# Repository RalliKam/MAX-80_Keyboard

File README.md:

# LOBO MAX-80 · Keyboard Logic Board

This KiCad 10 project recreates the keyboard logic board from sheet 5 of the original LOBO MAX-80 schematics. The board scans the keyboard matrix and connects the mainboard to the hard disk and parallel printer interfaces. It also carries the boot-selection DIP switch and reset button.

## Opening the project

Open [MAX-80-Keyboard.kicad_pro](MAX-80-Keyboard.kicad_pro) in KiCad 10. The [schematic](MAX-80-Keyboard.kicad_sch) shows the switch matrix and interface logic. The [PCB layout](MAX-80-Keyboard.kicad_pcb) contains 106 footprints, including 76 keyboard switches. PCB routing is still pending.

## Keyboard layout

The rebuild uses plate-mounted Cherry MX switches on a 19.05 mm pitch. The staggered rows follow the reference photo, with F1–F4 down the left side of the numeric keypad and Enter in its lower-right corner.

| Keys | Count | Keycap width |
| --- | ---: | ---: |
| Letters, digits, punctuation, and other single-width keys | 72 | 1u |
| Return and both Shift keys | 3 | 1.5u |
| Space bar | 1 | 8u |

The wide key sizes are estimates from the photo. The space bar stabilizer spacing and fit to the original case still need a physical check.

The numeric keypad shares matrix positions with the main keyboard. Switches K66–K76 implement the keypad digits and decimal point, each wired in parallel with its counterpart. Keypad Enter shares the Return matrix position. The original matrix is documented on page TS-17 of the [MAX-80 Technical Reference Manual](../MAX-80_MAINBOARD/Tech_Ref_Manual_Updated.pdf#page=65).

## Board connections

| Connector | Function | Footprint |
| --- | --- | --- |
| J7 | Mainboard interface | 34-pin male header, 2 × 17, 2.54 mm pitch |
| J8 | Winchester hard disk interface | 50-contact card edge |
| J9 | Parallel printer interface | 34-contact card edge |

## Libraries and original drawings

The project includes two [symbol libraries](sym-lib-table). The [keyboard footprint library](MAX80_KeyboardParts.pretty) contains the two card-edge connectors, reset switch, DO-7 diode, and 8u space bar footprint. Other parts use the standard KiCad libraries.

- [Original schematic, sheet 5](../MAX-80_MAINBOARD/5.png)
- [Original keyboard logic board placement drawing](../MAX-80_MAINBOARD/Keyboard%20logic%20board.png)
- [Companion CPU Logic Board project](../MAX-80_MAINBOARD/README.md)

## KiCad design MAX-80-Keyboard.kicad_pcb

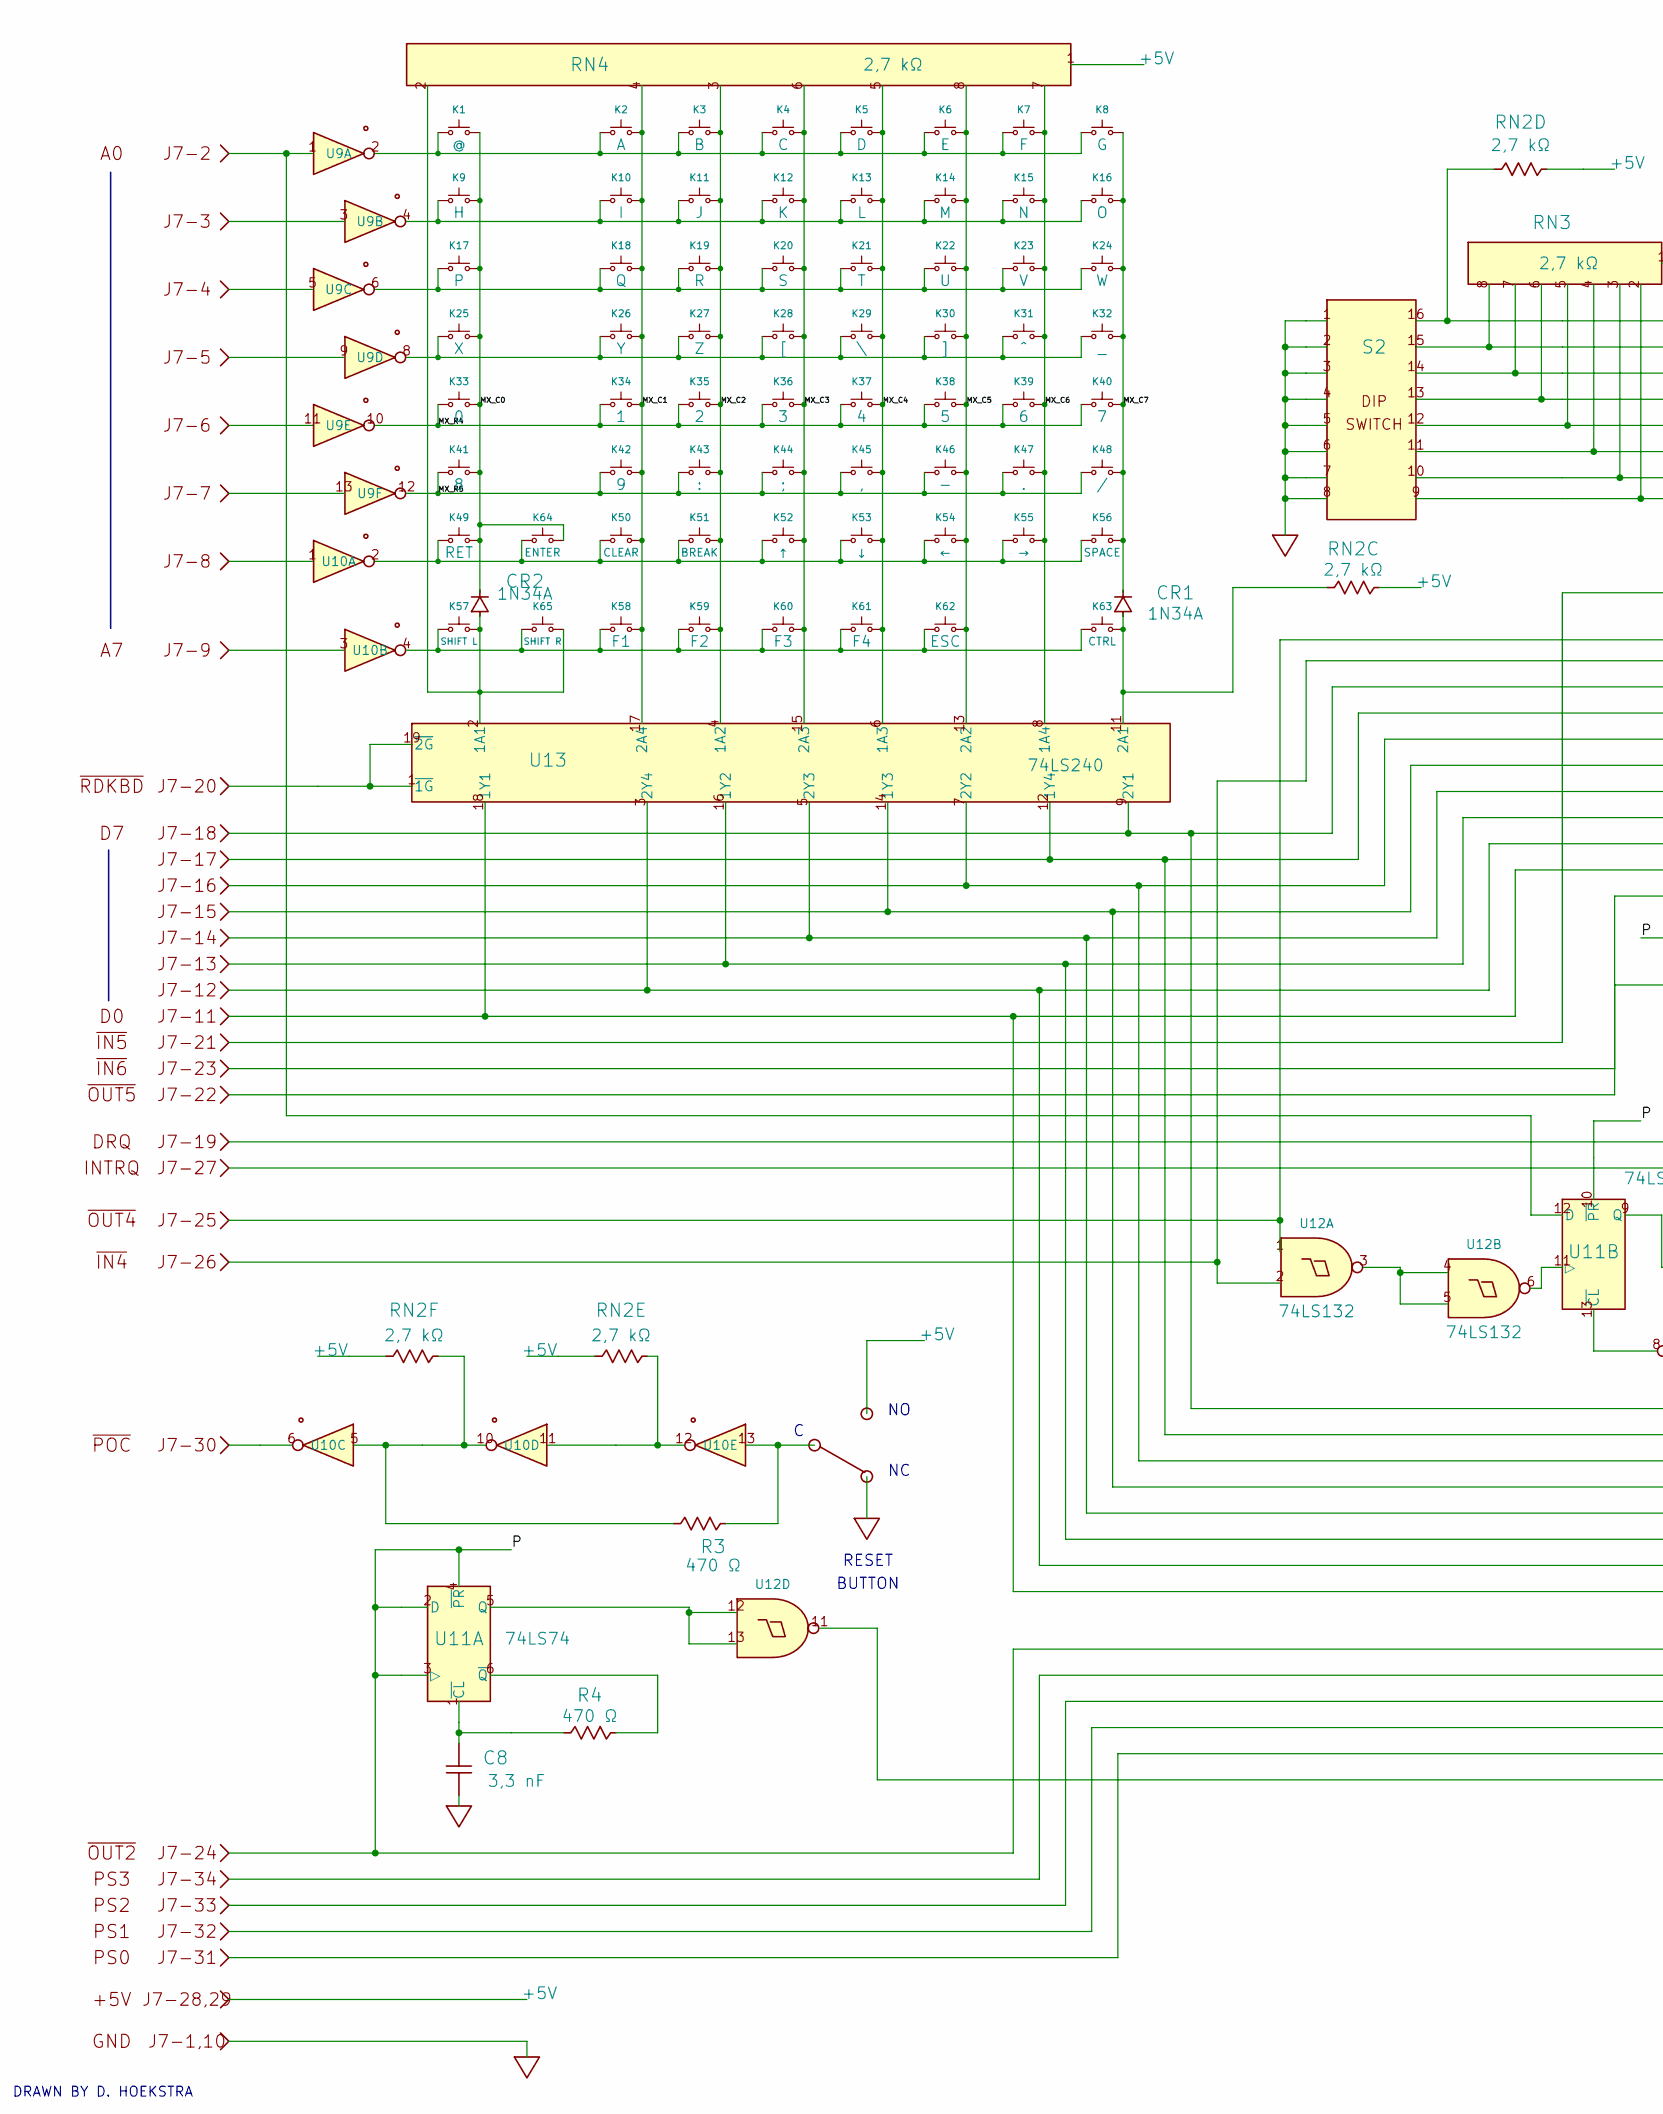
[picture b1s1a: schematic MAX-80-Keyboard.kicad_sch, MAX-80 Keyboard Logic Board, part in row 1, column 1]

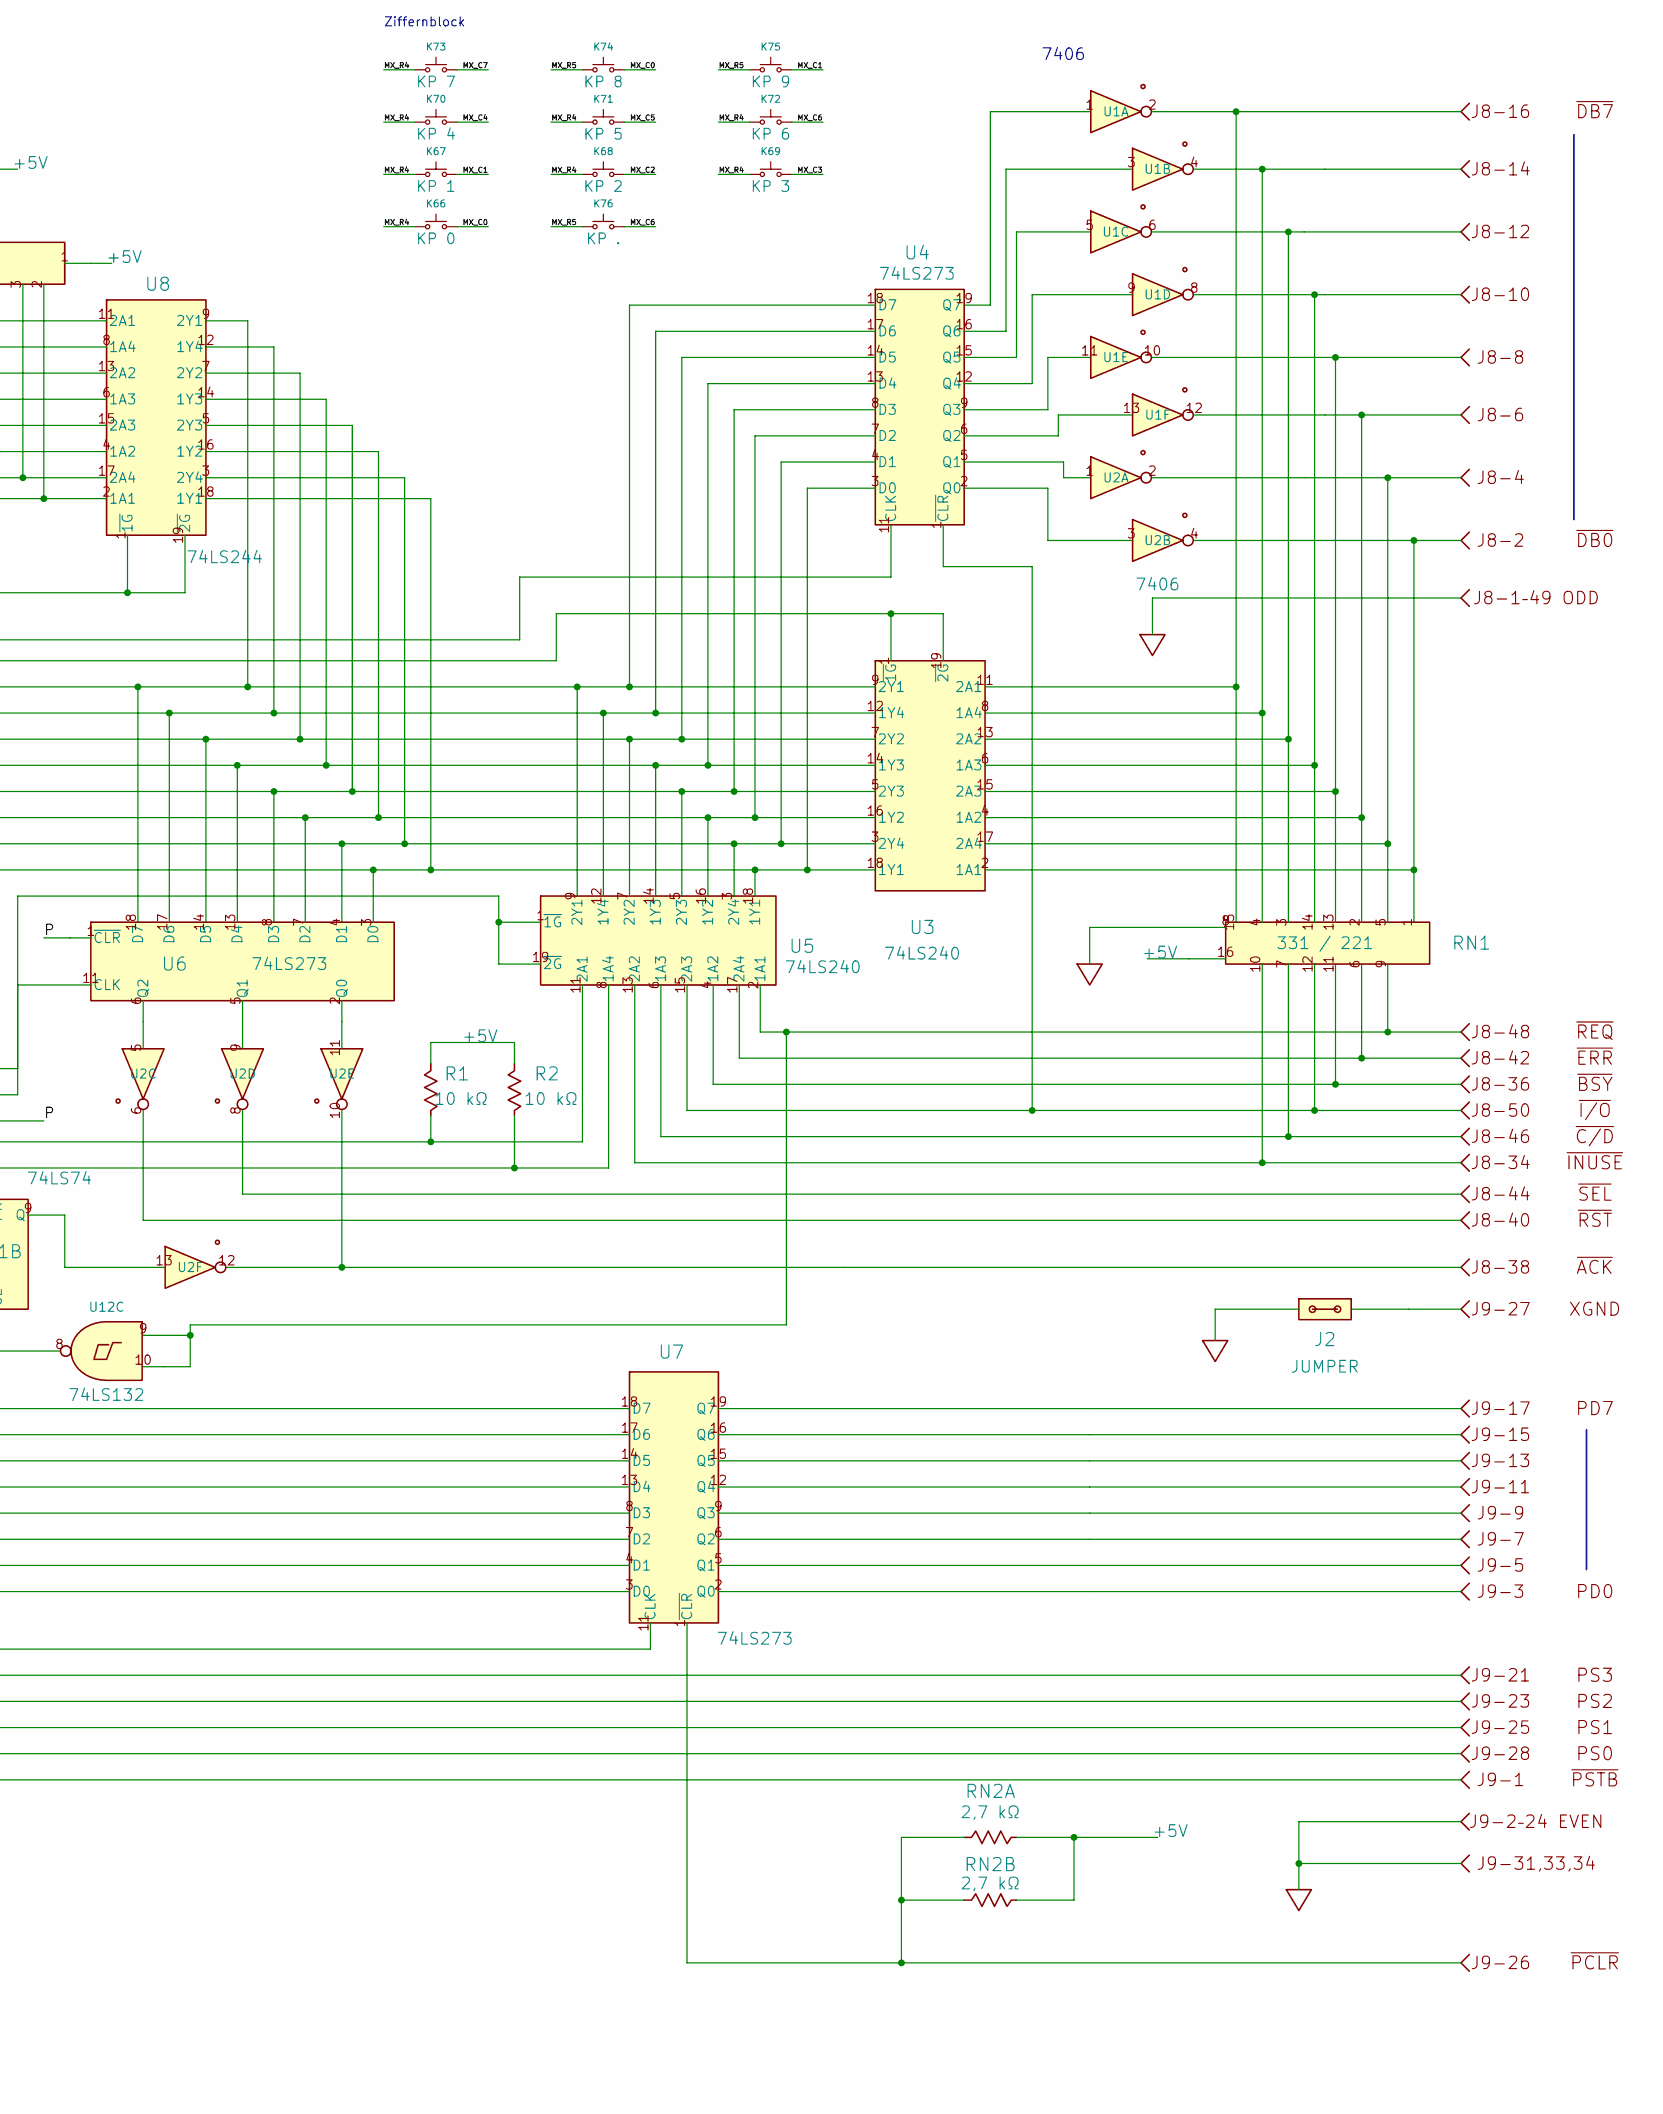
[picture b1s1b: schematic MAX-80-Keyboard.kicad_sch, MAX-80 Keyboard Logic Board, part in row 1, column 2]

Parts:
C8: 3,3 nF; C_Disc_D5.0mm_W2.5mm_P5.00mm
CR1, CR2: 1N34A; D_DO-7_P10.16mm_Horizontal
J2: JUMPER; PinHeader_1x02_P2.54mm_Vertical
J7: CPU-Verbindung; PinHeader_2x17_P2.54mm_Vertical
J8: Festplatte; Winchester_50Pin_P2.54mm_Key4-6
J9: Parallelport; Parallel_34Pin_P2.54mm_Key4-6
K1: @; SW_Cherry_MX_1.00u_Plate
K2: A; SW_Cherry_MX_1.00u_Plate
K3: B; SW_Cherry_MX_1.00u_Plate
K4: C; SW_Cherry_MX_1.00u_Plate
K5: D; SW_Cherry_MX_1.00u_Plate
K6: E; SW_Cherry_MX_1.00u_Plate
K7: F; SW_Cherry_MX_1.00u_Plate
K8: G; SW_Cherry_MX_1.00u_Plate
K9: H; SW_Cherry_MX_1.00u_Plate
K10: I; SW_Cherry_MX_1.00u_Plate
K11: J; SW_Cherry_MX_1.00u_Plate
K12: K; SW_Cherry_MX_1.00u_Plate
K13: L; SW_Cherry_MX_1.00u_Plate
K14: M; SW_Cherry_MX_1.00u_Plate
K15: N; SW_Cherry_MX_1.00u_Plate
K16: O; SW_Cherry_MX_1.00u_Plate
K17: P; SW_Cherry_MX_1.00u_Plate
K18: Q; SW_Cherry_MX_1.00u_Plate
K19: R; SW_Cherry_MX_1.00u_Plate
K20: S; SW_Cherry_MX_1.00u_Plate
K21: T; SW_Cherry_MX_1.00u_Plate
K22: U; SW_Cherry_MX_1.00u_Plate
K23: V; SW_Cherry_MX_1.00u_Plate
K24: W; SW_Cherry_MX_1.00u_Plate
K25: X; SW_Cherry_MX_1.00u_Plate
K26: Y; SW_Cherry_MX_1.00u_Plate
K27: Z; SW_Cherry_MX_1.00u_Plate
K28: [; SW_Cherry_MX_1.00u_Plate
K29: \; SW_Cherry_MX_1.00u_Plate
K30: ]; SW_Cherry_MX_1.00u_Plate
K31: ^; SW_Cherry_MX_1.00u_Plate
K32: _; SW_Cherry_MX_1.00u_Plate
K33: 0; SW_Cherry_MX_1.00u_Plate
K34: 1; SW_Cherry_MX_1.00u_Plate
K35: 2; SW_Cherry_MX_1.00u_Plate
K36: 3; SW_Cherry_MX_1.00u_Plate
K37: 4; SW_Cherry_MX_1.00u_Plate
K38: 5; SW_Cherry_MX_1.00u_Plate
K39: 6; SW_Cherry_MX_1.00u_Plate
K40: 7; SW_Cherry_MX_1.00u_Plate
K41: 8; SW_Cherry_MX_1.00u_Plate
K42: 9; SW_Cherry_MX_1.00u_Plate
K43: :; SW_Cherry_MX_1.00u_Plate
K44: ;; SW_Cherry_MX_1.00u_Plate
K45: ,; SW_Cherry_MX_1.00u_Plate
K46: -; SW_Cherry_MX_1.00u_Plate
K47: .; SW_Cherry_MX_1.00u_Plate
K48: /; SW_Cherry_MX_1.00u_Plate
K49: RET; SW_Cherry_MX_1.50u_Plate
K50: CLEAR; SW_Cherry_MX_1.00u_Plate
K51: BREAK; SW_Cherry_MX_1.00u_Plate
K52: ↑; SW_Cherry_MX_1.00u_Plate
K53: ↓; SW_Cherry_MX_1.00u_Plate
K54: ←; SW_Cherry_MX_1.00u_Plate
K55: →; SW_Cherry_MX_1.00u_Plate
K56: SPACE; SW_Cherry_MX_8.00u_Plate_MAX80
K57: SHIFT L; SW_Cherry_MX_1.50u_Plate
K58: F1; SW_Cherry_MX_1.00u_Plate
K59: F2; SW_Cherry_MX_1.00u_Plate
K60: F3; SW_Cherry_MX_1.00u_Plate
K61: F4; SW_Cherry_MX_1.00u_Plate
K62: ESC; SW_Cherry_MX_1.00u_Plate
K63: CTRL; SW_Cherry_MX_1.00u_Plate
K64: ENTER; SW_Cherry_MX_1.00u_Plate
K65: SHIFT R; SW_Cherry_MX_1.50u_Plate
K66: KP 0; SW_Cherry_MX_1.00u_Plate
K67: KP 1; SW_Cherry_MX_1.00u_Plate
K68: KP 2; SW_Cherry_MX_1.00u_Plate
K69: KP 3; SW_Cherry_MX_1.00u_Plate
K70: KP 4; SW_Cherry_MX_1.00u_Plate
K71: KP 5; SW_Cherry_MX_1.00u_Plate
K72: KP 6; SW_Cherry_MX_1.00u_Plate
K73: KP 7; SW_Cherry_MX_1.00u_Plate
K74: KP 8; SW_Cherry_MX_1.00u_Plate
K75: KP 9; SW_Cherry_MX_1.00u_Plate
K76: KP .; SW_Cherry_MX_1.00u_Plate
R1, R2: 10 kΩ; R_Axial_DIN0207_L6.3mm_D2.5mm_P7.62mm_Horizontal
R3, R4: 470 Ω; R_Axial_DIN0207_L6.3mm_D2.5mm_P7.62mm_Horizontal
RN1: 331 / 221; DIP-16_W7.62mm
RN2, RN3, RN4: 2,7 kΩ; R_Array_SIP8
S1: RESET; Reset_800UDP8P1A1M6
S2: DIP-Schalter 8-fach; SW_DIP_SPSTx08_Slide_9.78x22.5mm_W7.62mm_P2.54mm
U1, U2: 7406; DIP-14_W7.62mm
U3, U5, U13: 74LS240; DIP-20_W7.62mm
U4, U6, U7: 74LS273; DIP-20_W7.62mm
U8: 74LS244; DIP-20_W7.62mm
U9, U10: 74LS05; DIP-14_W7.62mm
U11: 74LS74; DIP-14_W7.62mm
U12: 74LS132; DIP-14_W7.62mm

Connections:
+5V: J7.28, J7.29, R1.1, R2.1, RN1.16 (+5V), RN2.1, RN3.1, RN4.1, S1.2 (NO), U1.14 (+5V), U2.14 (+5V), U3.20 (+5V), U4.20 (+5V), U5.20 (+5V), U6.20 (+5V), U7.20 (+5V), U8.20 (+5V), U9.14 (+5V), U10.14 (+5V), U11.14 (+5V), U12.14 (+5V), U13.20 (+5V)
/MX_C0: CR2.1, K1.2, K9.2, K17.2, K25.2, K33.2, K41.2, K49.2, K64.2, K66.2, K74.2
/MX_C1: K2.2, K10.2, K18.2, K26.2, K34.2, K42.2, K50.2, K58.2, K67.2, K75.2, RN4.4, U13.17 (2A4)
/MX_C2: K3.2, K11.2, K19.2, K27.2, K35.2, K43.2, K51.2, K59.2, K68.2, RN4.3, U13.4 (1A2)
/MX_C3: K4.2, K12.2, K20.2, K28.2, K36.2, K44.2, K52.2, K60.2, K69.2, RN4.6, U13.15 (2A3)
/MX_C4: K5.2, K13.2, K21.2, K29.2, K37.2, K45.2, K53.2, K61.2, K70.2, RN4.5, U13.6 (1A3)
/MX_C5: K6.2, K14.2, K22.2, K30.2, K38.2, K46.2, K54.2, K62.2, K71.2, RN4.8, U13.13 (2A2)
/MX_C6: K7.2, K15.2, K23.2, K31.2, K39.2, K47.2, K55.2, K72.2, K76.2, RN4.7, U13.8 (1A4)
/MX_C7: CR1.1, K8.2, K16.2, K24.2, K32.2, K40.2, K48.2, K56.2, K73.2
/MX_R4: K33.1, K34.1, K35.1, K36.1, K37.1, K38.1, K39.1, K40.1, K66.1, K67.1, K68.1, K69.1, K70.1, K71.1, K72.1, K73.1, U9.10
/MX_R5: K41.1, K42.1, K43.1, K44.1, K45.1, K46.1, K47.1, K48.1, K74.1, K75.1, K76.1, U9.12
/P: J7.24, U6.1 (~CLR), U7.11 (CLK), U11.2 (D), U11.3 (▷), U11.4 (~PR), U11.10 (~PR)
GND: C8.2, J2.1, J7.1, J7.10, J8.1, J8.3, J8.5, J8.7, J8.9, J8.11, J8.13, J8.15, J8.17, J8.19, J8.21, J8.23, J8.25, J8.27, J8.29, J8.31, J8.33, J8.35, J8.37, J8.39, J8.41, J8.43, J8.45, J8.47, J8.49, J9.2, J9.4, J9.6, J9.8, J9.10, J9.12, J9.14, J9.16, J9.18, J9.20, J9.22, J9.24, J9.31, J9.33, J9.34, RN1.8 (GND), S1.3 (NC), S2.1, S2.2, S2.3, S2.4, S2.5, S2.6, S2.7, S2.8, U1.7 (GND), U2.7 (GND), U3.10 (GND), U4.10 (GND), U5.10 (GND), U6.10 (GND), U7.10 (GND), U8.10 (GND), U9.7 (GND), U10.7 (GND), U11.7 (GND), U12.7 (GND), U13.10 (GND)
unnamed: J2.2, J9.27
unnamed: J7.3, U9.3
unnamed: J7.4, U9.5
unnamed: J7.5, U9.9
unnamed: J7.6, U9.11
unnamed: J7.7, U9.13
unnamed: J7.8, U10.1
unnamed: J7.9, U10.3
unnamed: J7.30, U10.6
unnamed: J7.31, J9.28
unnamed: J7.32, J9.25
unnamed: J7.33, J9.23
unnamed: J7.34, J9.21
unnamed: J8.38, U2.10, U2.12
unnamed: J8.40, U2.6
unnamed: J8.44, U2.8
unnamed: J9.1, U12.11
unnamed: K1.1, K2.1, K3.1, K4.1, K5.1, K6.1, K7.1, K8.1, U9.2
unnamed: K9.1, K10.1, K11.1, K12.1, K13.1, K14.1, K15.1, K16.1, U9.4
unnamed: K17.1, K18.1, K19.1, K20.1, K21.1, K22.1, K23.1, K24.1, U9.6
unnamed: K25.1, K26.1, K27.1, K28.1, K29.1, K30.1, K31.1, K32.1, U9.8
unnamed: K49.1, K50.1, K51.1, K52.1, K53.1, K54.1, K55.1, K56.1, K64.1, U10.2
unnamed: K57.1, K58.1, K59.1, K60.1, K61.1, K62.1, K63.1, K65.1, U10.4
unnamed: R3.1, RN2.7, U10.5, U10.10
unnamed: J8.36, RN1.11 (BSY), U5.4 (1A2)
unnamed: J8.46, RN1.7 (C/D), U5.6 (1A3)
unnamed: J8.2, RN1.1 (DB0), U2.4, U3.2 (1A1)
unnamed: J8.4, RN1.5 (DB1), U2.2, U3.17 (2A4)
unnamed: J8.6, RN1.2 (DB2), U1.12, U3.4 (1A2)
unnamed: J8.8, RN1.13 (DB3), U1.10, U3.15 (2A3)
unnamed: J8.10, RN1.14 (DB4), U1.8, U3.6 (1A3)
unnamed: J8.12, RN1.3 (DB5), U1.6, U3.13 (2A2)
unnamed: J8.14, RN1.4 (DB6), U1.4, U3.8 (1A4)
unnamed: J8.16, RN1.15 (DB7), U1.2, U3.11 (2A1)
unnamed: J8.42, RN1.6 (ERR), U5.17 (2A4)
unnamed: J8.50, RN1.12 (I/O), U4.1 (~CLR), U5.15 (2A3)
unnamed: J8.34, RN1.10 (INUSE), U5.13 (2A2)
unnamed: J8.48, RN1.9 (REQ), U5.2 (1A1), U12.9, U12.10
unnamed: RN2.6, U10.11, U10.12
unnamed: R3.2, S1.1 (C), U10.13
unnamed: J7.26, U3.1 (~1G), U3.19 (~2G), U12.2
unnamed: J7.25, U4.11 (CLK), U12.1
unnamed: U2.3, U4.2 (Q0)
unnamed: U2.1, U4.5 (Q1)
unnamed: U1.13, U4.6 (Q2)
unnamed: U1.11, U4.9 (Q3)
unnamed: U1.9, U4.12 (Q4)
unnamed: U1.5, U4.15 (Q5)
unnamed: U1.3, U4.16 (Q6)
unnamed: U1.1, U4.19 (Q7)
unnamed: J7.27, R2.2, U5.8 (1A4)
unnamed: J7.19, R1.2, U5.11 (2A1)
unnamed: J7.23, U5.1 (~1G), U5.19 (~2G)
unnamed: J7.22, U6.11 (CLK)
unnamed: U2.11, U6.2 (Q0)
unnamed: U2.9, U6.5 (Q1)
unnamed: U2.5, U6.6 (Q2)
unnamed: J9.3, U7.2 (Q0)
unnamed: J9.5, U7.5 (Q1)
unnamed: J9.7, U7.6 (Q2)
unnamed: J9.9, U7.9 (Q3)
unnamed: J9.11, U7.12 (Q4)
unnamed: J9.13, U7.15 (Q5)
unnamed: J9.15, U7.16 (Q6)
unnamed: J9.17, U7.19 (Q7)
unnamed: J9.26, RN2.2, RN2.3, U7.1 (~CLR)
unnamed: RN3.2, S2.9, U8.2 (1A1)
unnamed: RN3.4, S2.11, U8.4 (1A2)
unnamed: RN3.6, S2.13, U8.6 (1A3)
unnamed: RN3.8, S2.15, U8.8 (1A4)
unnamed: RN2.4, S2.16, U8.11 (2A1)
unnamed: RN3.7, S2.14, U8.13 (2A2)
unnamed: RN3.5, S2.12, U8.15 (2A3)
unnamed: RN3.3, S2.10, U8.17 (2A4)
unnamed: J7.21, U8.1 (~1G), U8.19 (~2G)
unnamed: U11.5 (Q), U12.12, U12.13
unnamed: C8.1, R4.2, U11.1 (~CL)
unnamed: R4.1, U11.6 (~Q)
unnamed: J7.2, U9.1, U11.12 (D)
unnamed: U2.13, U11.9 (Q)
unnamed: U11.13 (~CL), U12.8
unnamed: U11.11 (▷), U12.6
unnamed: U12.3, U12.4, U12.5
unnamed: CR2.2, K57.2, K65.2, RN4.2, U13.2 (1A1)
unnamed: J7.11, U3.18 (1Y1), U4.3 (D0), U5.18 (1Y1), U6.3 (D0), U7.3 (D0), U8.18 (1Y1), U13.18 (1Y1)
unnamed: J7.13, U3.16 (1Y2), U4.7 (D2), U5.16 (1Y2), U6.7 (D2), U7.7 (D2), U8.16 (1Y2), U13.16 (1Y2)
unnamed: J7.15, U3.14 (1Y3), U4.13 (D4), U5.14 (1Y3), U6.13 (D4), U7.13 (D4), U8.14 (1Y3), U13.14 (1Y3)
unnamed: J7.17, U3.12 (1Y4), U4.17 (D6), U5.12 (1Y4), U6.17 (D6), U7.17 (D6), U8.12 (1Y4), U13.12 (1Y4)
unnamed: CR1.2, K63.2, RN2.5, U13.11 (2A1)
unnamed: J7.18, U3.9 (2Y1), U4.18 (D7), U5.9 (2Y1), U6.18 (D7), U7.18 (D7), U8.9 (2Y1), U13.9 (2Y1)
unnamed: J7.16, U3.7 (2Y2), U4.14 (D5), U5.7 (2Y2), U6.14 (D5), U7.14 (D5), U8.7 (2Y2), U13.7 (2Y2)
unnamed: J7.14, U3.5 (2Y3), U4.8 (D3), U5.5 (2Y3), U6.8 (D3), U7.8 (D3), U8.5 (2Y3), U13.5 (2Y3)
unnamed: J7.12, U3.3 (2Y4), U4.4 (D1), U5.3 (2Y4), U6.4 (D1), U7.4 (D1), U8.3 (2Y4), U13.3 (2Y4)
unnamed: J7.20, U13.1 (~1G), U13.19 (~2G)

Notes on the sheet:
7406
RESET
BUTTON
DRAWN BY D. HOEKSTRA
Ziffernblock

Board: 2 copper layers, 106 parts (1 on the bottom side), 107 nets, no tracks yet.
